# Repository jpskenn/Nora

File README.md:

# Nora（ノラ）

Nora（ノラ）は、Choc v1 ロープロファイルスイッチを使用する、狭ピッチの一体型キーボードです。  
姉妹機[Jones（ジョーンズ）](https://github.com/jpskenn/Jones)と同様の、2行目と3行目にずれのない左右対称の配列が特徴です。  
専用のボトムプレートや、GH60型，Poker型のロープロファイルケースと組み合わせて使用できます。

名前の由来は、”狭ピッチのJonesキーボード”からの連想で…

``` text
狭ピッチのJones → ナロー・ジョーンズ → ノラ・ジョーンズ → ノラ

Narrow Jones --> Norah Jones --> Norah --> Nora
```

という具合の言葉遊びで、Nora（ノラ）に決まりました。

Nora is a narrow pitch keyboard with Choc v1 low profile switches.  
It has symmetrical gapless R2-R3 row, like [Jones](https://github.com/jpskenn/Jones).  
Original bottom plate and GH60/Poker compatible low profile cases are supported.

---

<!-- @import "[TOC]" {cmd="toc" depthFrom=2 depthTo=2 orderedList=false} -->

<!-- code_chunk_output -->

- [対象とするユーザー](#対象とするユーザー)
- [コンセプト](#コンセプト)
- [特徴](#特徴)
- [機能](#機能)
- [ビルドガイド](#ビルドガイド)
- [ビルド例](#ビルド例)
- [製作歴](#製作歴)

<!-- /code_chunk_output -->

---

## 対象とするユーザー

このNoraキーボードは、  
*”一般的なキーボードのキー配列に不満があり、より良いタイピングポジションを求めている方”*  
を対象に作られています。

特に、  
*”一般的なキーボードと違いすぎないキーボードを求めている方”*  
におすすめします。

## コンセプト

- 「Chocスイッチの狭ピッチを60%ケースに入れたら、1列増えて65%キーボードができちゃうのでは？」という思いつき。
- 一般的なキーピッチの19.05mmで打鍵がつらいのを、狭ピッチで楽にしたい。
- 「狭ピッチは浅いストロークの方が打鍵しやすい」という経験から、Chocスイッチを採用。
- MBKキーキャップって格好良いじゃんか。
- Jonesの横方向（行方向）のずれかたや、左右対称のアルファ部に満足している。
- 一般的なキーボードのレイアウトから大きく変えずに、打鍵しやすくする。
- キー数は60%くらいで、数字行がついているものが使いたい。
- GH60型のケースに対応させ、ケース設計をメイン作業に含めない。
- これくらいの狭ピッチなら、通常のキーボードと何ら変わらず打鍵できることを伝えたい。

## 特徴

### 狭ピッチ

Kailh Chocスイッチとそれに対応するキーキャップを使用することで、一般的なキーボードよりもキーピッチが狭くなっています。

60%キーボードのサイズに16列を配置するため、Choc用キーキャップのキーピッチ（たて17mm×よこ18mm）よりも横方向を少し狭く（たて17mm×よこ約17.86mm）しています。  
横方向のキーピッチは、MBKまたはそれ以下のサイズのChoc用キーキャップの使用を前提とした設計です。

キーピッチの比較  
上：一般的なキーピッチの60%キーボード、HHKB Professional。5行15列。  
下：狭ピッチ設計のNora。5行**16列**（1列多い）。

### 左右対称のキーレイアウト

キーレイアウトは[Jones](https://github.com/jpskenn/Jones)のレイアウトを元に設計しており、2行目と3行目にずれのない左右対称のキーレイアウトです。  

Jones（上）とNora（下）。  
どちらも2行目と3行目にずれがなく、左右対称。

詳しくは次の項目を参照してください。

- [Jones#独自のずれ幅をもつ左右対象のアルファ部](https://github.com/jpskenn/Jones#独自のずれ幅をもつ左右対象のアルファ部)

### レイアウトのスタイル、バリエーション

狭ピッチの一体型キーボードというコンセプトを元に、ふたつのレイアウトスタイルを作成しました。

- Nora, Fearless Wings
- Nora, 1.8k

各スタイルの特徴は以下の通りです。

#### Nora, Fearless Wings

左右に大きく離れたアルファ部が特徴のレイアウトスタイルです。  
[Keyboard Layout Editor: Nora, Fearless Wings family](http://www.keyboard-layout-editor.com/#/gists/568990362f215776aa93e3b90064f241)

アルファ部を左右へ大きく離すことで打鍵時の肘・腕・手首・指先の位置を最適化し、快適な運指と、肩や腕への負担軽減を目指しています。  
手首をあまり持ち上げないスタイルでも快適に打鍵できるように、最下行の左右の端にはキーを配置せず、手のひらにキーが当たる不快感を無くしています。  
`Z`キーを外側へずらして、[SemiErgo](https://github.com/mtei/SemiErgo_Layout)のような完全に左右対称のレイアウトも構成できます。

キー配置とロータリーエンコーダの有無により、3つのバリエーションがあります。

- Fullレイアウト

    左右に離れたアルファ部の間を、すべて埋めたレイアウトです。  
    65〜70%キーボードに相当する71個のキーは、多くのキーを必要とする方に適しています。  
    中央部に記号キーやカーソルを配置したり、テンキーやマクロキーを配置したりできます。

- FWレイアウト

    Fullレイアウトから中央部の7キーを取り除き、真ん中に隙間のあるレイアウトです。  
    60%キーボードに相当する64キーをもち、必要十分なキー数を確保しています。  
    ホームポジションから手を移動させず、レイヤー内のキーを打鍵するのが快適な方に適しています。  

- REレイアウト

    FWレイアウトの中央にロータリーエンコーダを配置したレイアウトです。  
    4行目の中央をFWレイアウトから2キー減らし、直径35ｍｍまでのノブに対応しています。

#### Nora, 1.8k

アルファ部の右側にテンキーを配置し、少し下へ飛びだしたカーソルキーが特徴のレイアウトスタイルです。  
[Keyboard Layout Editor: Nora](http://www.keyboard-layout-editor.com/#/gists/f8d08df6aa77dcdd6d3cb7350a545df7)

一般的なキーボードをコンパクトにまとめたようなキー配置になっています。  
キー数が多く、記号やカーソルなどを物理的に配置することができます。

試作版でロードテストをおこなった結果、狭ピッチで左右の手が中央へ近づいて肩や腕、親指まわりが窮屈になり、長時間の使用には向かないことがわかりました。  
日常的に使用する上での快適さを満たせないため、1.8kは開発を停止しています。

## 機能

### QMKファームウェアによる動作

MCUにATmega32u4を採用し、[QMKファームウェア](https://github.com/qmk/qmk_firmware)によって動作します。

### RemapやVIAなどのキーマップ書き換えツールに対応

[Remap](https://remap-keys.app)や[VIA](https://caniusevia.com)などのキーマップ書き換えツールに対応しており、ファームウェアを書き換えることなく、キーの割り当てを変更することができます。  

### EEPROM搭載により、多くのレイヤーを使用可能

外部EEPROMを搭載したことで、RemapやVIA使用時にも多くのレイヤーを使用することができます。  
出荷時に書き込まれている初期ファームウェアでは、10個のレイヤーを使用可能です。  

### ケース

キット同梱のボトムプレートと組み合わせれば、ケースレスで使用できます。  
ケースを使用する場合に比べてキーボードの高さを低く抑えることができ、手首の負担軽減などに有効です。

また、GH60型やPoker型に互換性のある、ロープロファイルケースと組み合わせて使用することもできます。  
→[ビルド例](#ビルド例)  

### フルキーバックライトLED

レイヤーの状態を表示するインジケータや、イルミネーションとして使用できるキーバックライトLEDを、すべてのキーへ取り付けできます。

### Raspberry Pi PICOによる動作（実験的機能）

実験的機能として、Raspberry Pi PICOで動作させることができます。  
キーマトリクス、LED、I2Cに配線をつないであるので、DIYで楽しんでください。

[PRK Firmware](https://github.com/picoruby/prk_firmware)を使用して、キー入力とLEDの点灯を確認済みです。

## ビルドガイド

- 最新版
  - [Nora, Fearless Wings v.1(DN0032) ビルドガイド](./docs/BuildGuide_DN0032_JA.md)

- 過去版
  - [Nora, Fearless Wings DN0031 ビルドガイド](./docs/BuildGuide_DN0031_JA.md)
  - [Nora, Fearless Wings DN0030 ビルドガイド](./docs/BuildGuide_DN0030_JA.md)
  - [Nora, 1.8k v.0.1 ビルドガイド](./docs/BuildGuide_v.0.1_JA.md)

</details>

## ビルド例

| ビルド例 | 詳細 |
| --- | :-- |
|  | v.1(DN0032)<br>layout: Full<br>keycaps: MBK Legend‡ Glow<br>case: Bottom plate |
|  | DN0031<br>layout: FW<br>keycaps: Kailh low profile + MBK<br>case: Bottom plate |
|  | DN0031<br>layout: RE<br>keycaps: Gravity Keycaps + MBK<br>case: KBDfans 60% Aluminum Low Profile, Gray |
|  | DN0020<br>layout: 1.8k<br>keycaps: MBK Colors & Self Dye<br>case: KBDfans 60% Aluminum Low Profile, Gray |
|  | DN0010<br>layout: 1.8k<br>keycaps: Kailh low profile<br>case: Bottom plate |

## 製作歴

- Fearless Wings v.1(DN0032), 2022年3月中旬

    組み立てやすさを向上。  
    ロータリーエンコーダのノブサイズ拡大のため、REレイアウトの最下行中央のキーを削除。  
    細部を調整。  
    DN0031組み立てアンケートの内容を反映。

- Fearless Wings DN0031, 2022年1月下旬

    スペースキーより内側のキーに親指が届きやすいように、最下行を外側へ0.25u移動。  
    ロータリーエンコーダ付きのレイアウトを追加。  
    組み立てやすさを向上。
    少数頒布。

- Fearless Wings DN0030, 2022年1月上旬

    DN0020を元にレイアウトを変更。  
    全キーへLEDを配置。  
    Jonesとの共用ボトムプレートを、PICOの取り付けに対応する切り欠きをつけて更新。

- 1.8k DN0020, 2021年12月中旬

    1.8k v.0.1の試作結果を反映。  
    全キーをKailhソケットに変更。  
    現在のところ基板設計のみ。未製造。

- 1.8k v.0.1, 2021年12月上旬

    試作1号機、完成。

- 1.8k v.0, 2021年11月上旬

    60%ケースにChocスイッチを配置して、65%キーボードにするアイデアを思いつく。

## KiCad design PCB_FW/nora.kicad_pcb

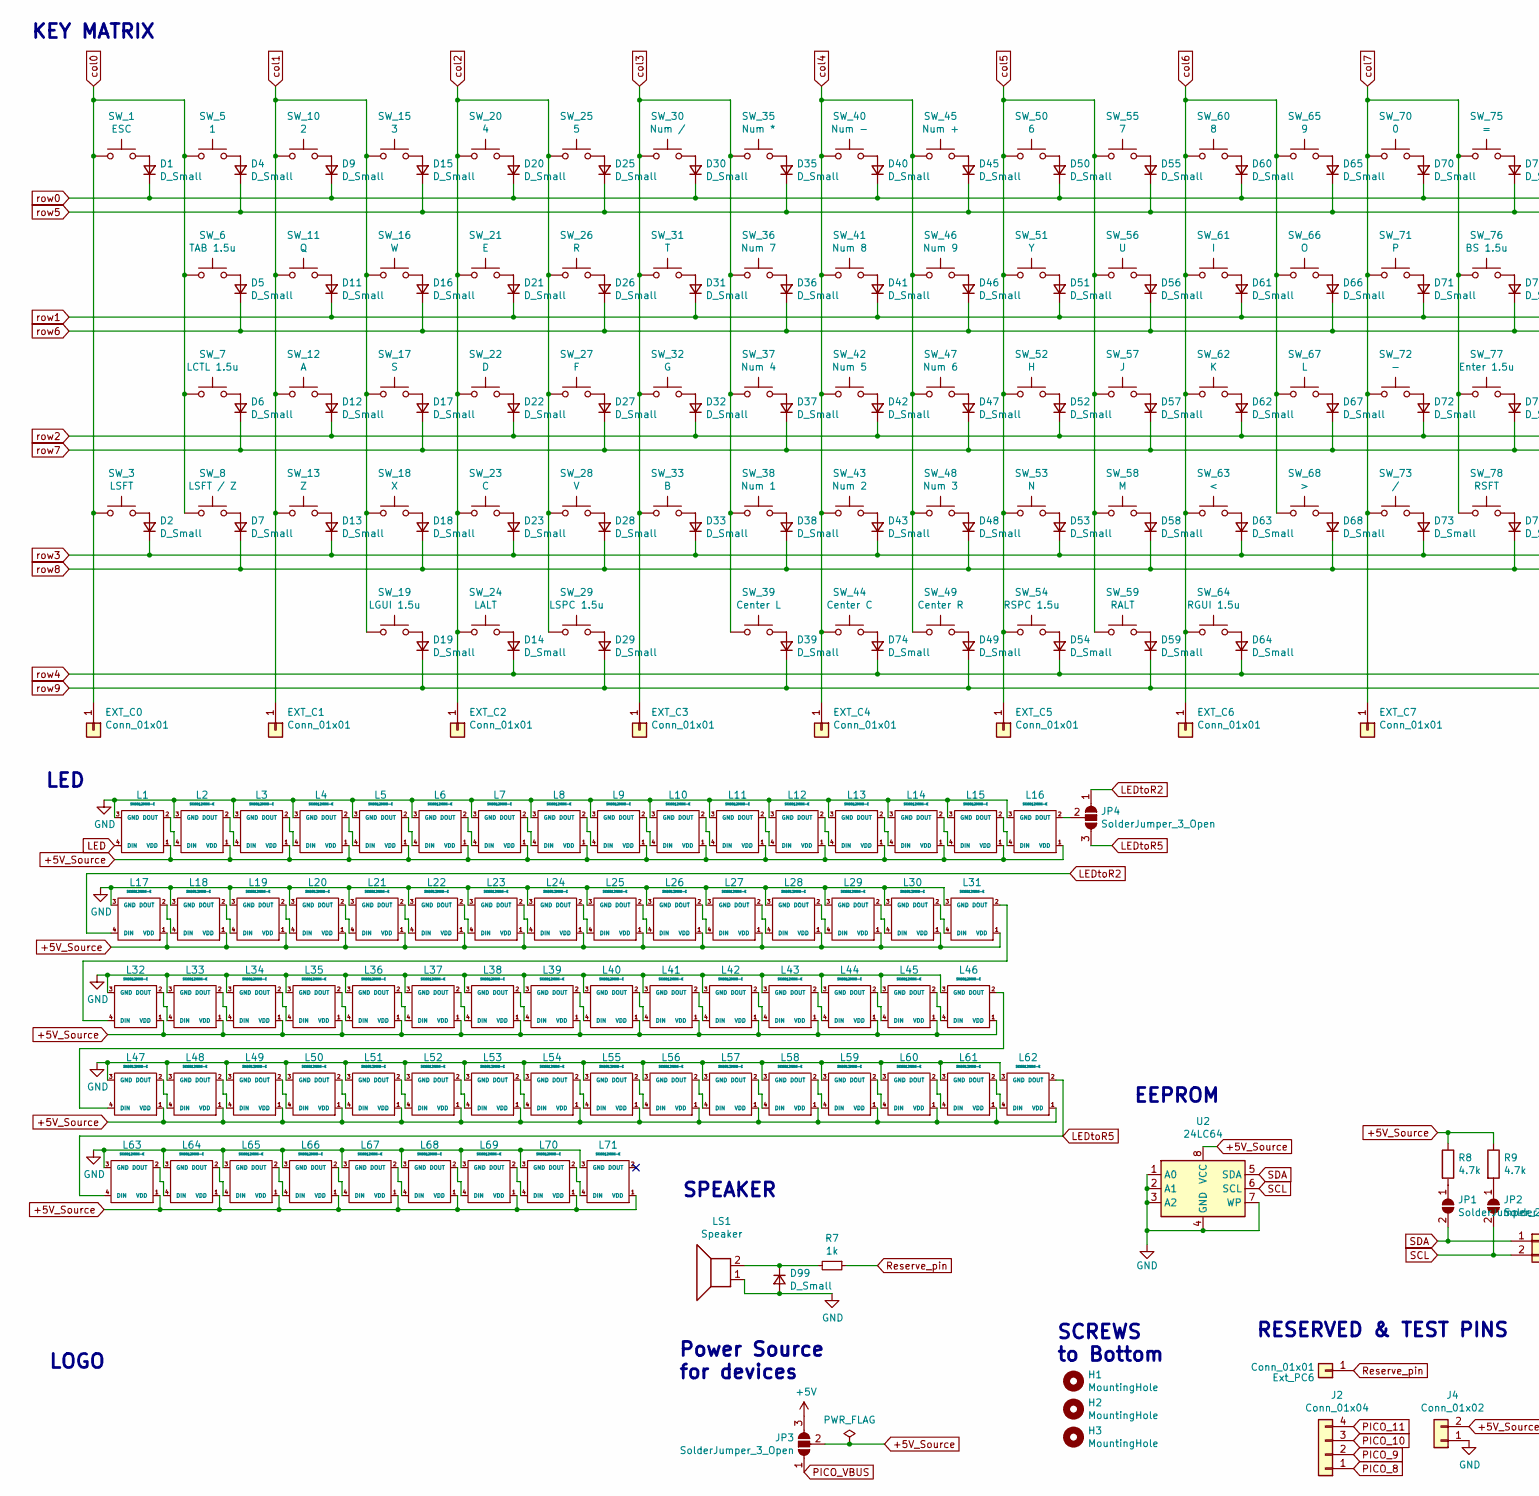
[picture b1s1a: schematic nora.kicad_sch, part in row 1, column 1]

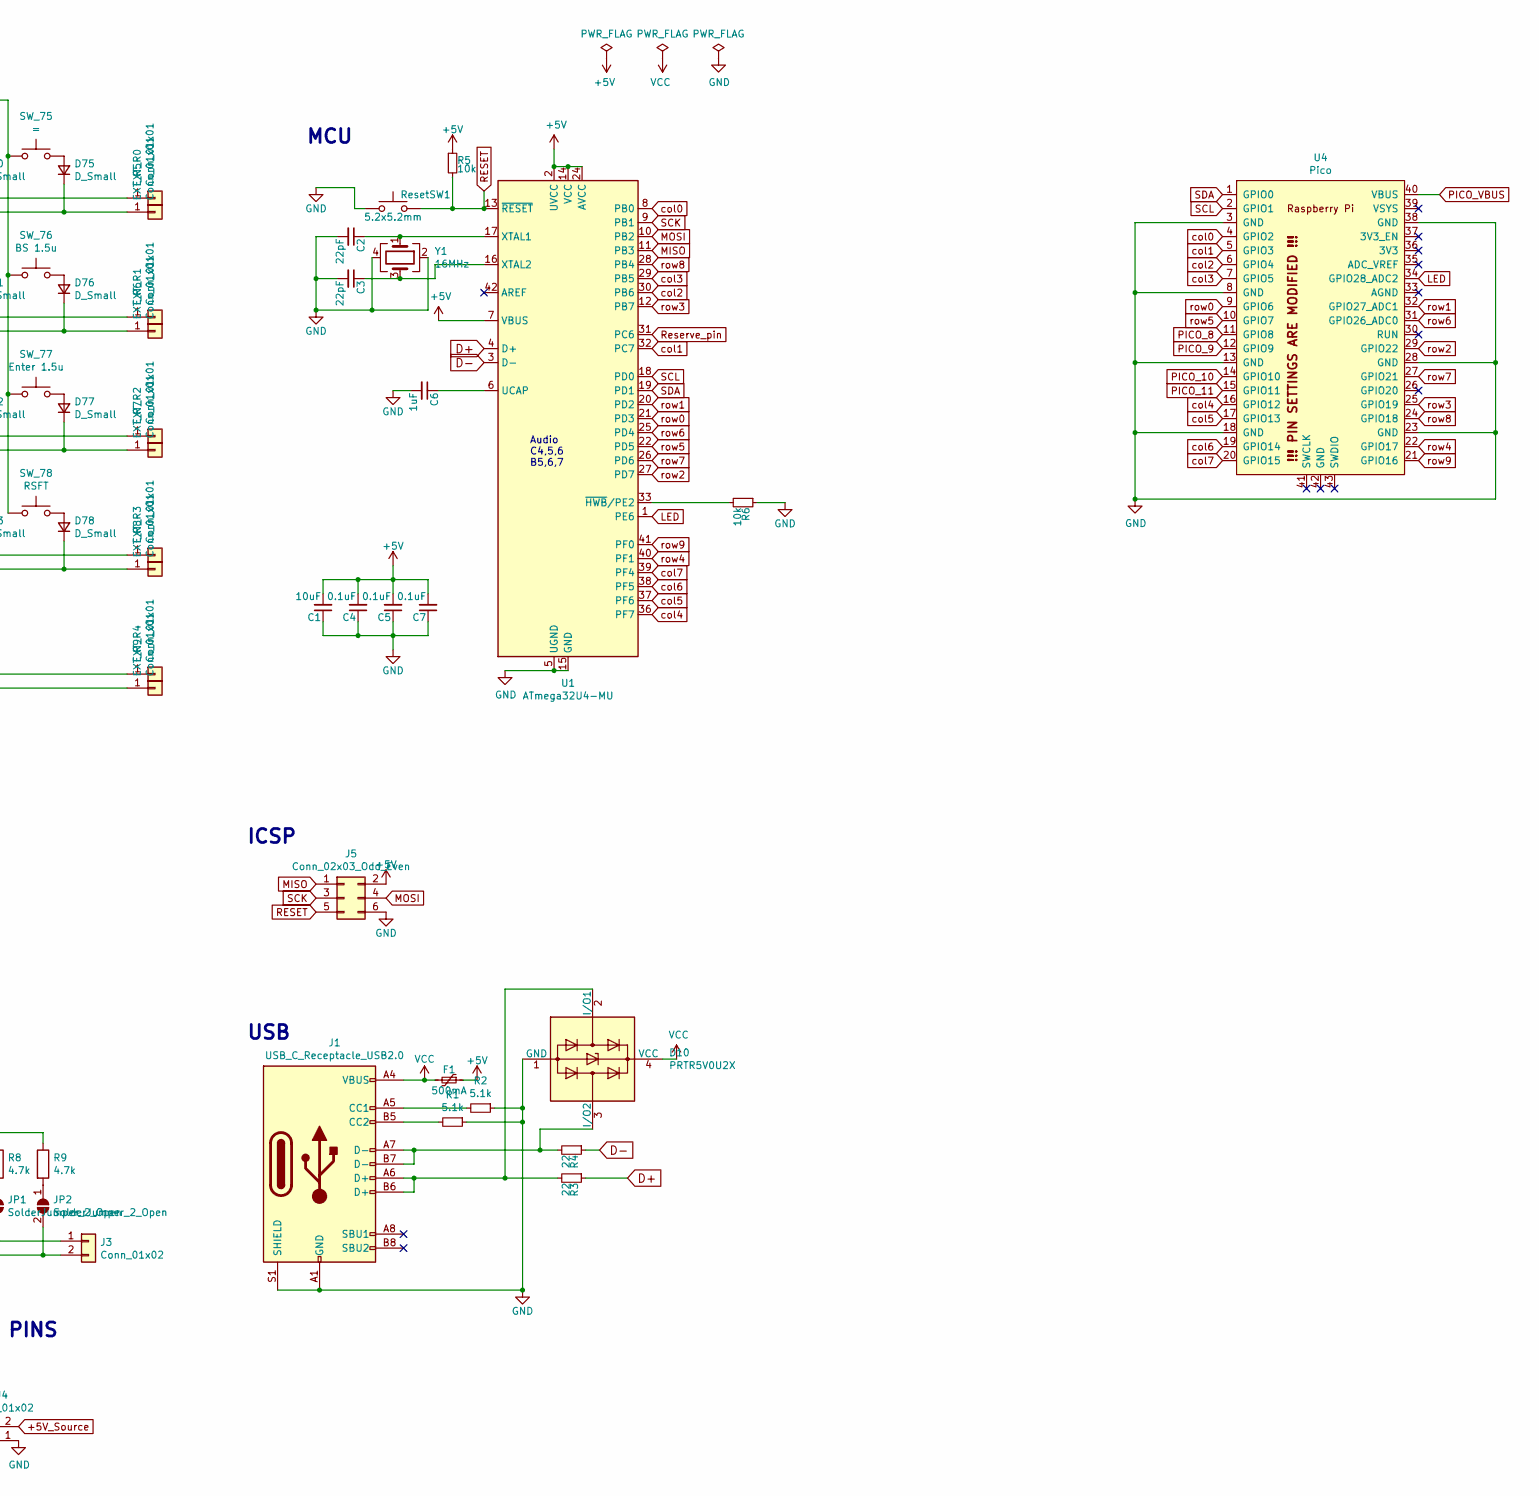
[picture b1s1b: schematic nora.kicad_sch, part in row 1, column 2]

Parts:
C1: 10uF; C_0805_2012Metric_Pad1.18x1.45mm_HandSolder; LCSC C15850
C2, C3: 22pF; C_0805_2012Metric_Pad1.18x1.45mm_HandSolder; LCSC C1804
C4, C5, C7: 0.1uF; C_0805_2012Metric_Pad1.18x1.45mm_HandSolder; LCSC C49678
C6: 1uF; C_0805_2012Metric_Pad1.18x1.45mm_HandSolder; LCSC C28323
D1, D2, D4, D5, D6, D7, D9, D11, D12, D13, D14, D15, D16, D17, D18, D19, D20, D21, D22, D23, D25, D26, D27, D28, D29, D30, D31, D32, D33, D35, D36, D37, D38, D39, D40, D41, D42, D43, D45, D46, D47, D48, D49, D50, D51, D52, D53, D54, D55, D56, D57, D58, D59, D60, D61, D62, D63, D64, D65, D66, D67, D68, D70, D71, D72, D73, D74, D75, D76, D77, D78: D_Small; D_SOD-123-Pretty_No_Reference; LCSC C81598
D10: PRTR5V0U2X; SOT-143; LCSC C78442
D99: D_Small; D_SOD-123-Pretty_No_Reference
EXT_C0, EXT_C1, EXT_C2, EXT_C3, EXT_C4, EXT_C5, EXT_C6, EXT_C7: Conn_01x01; TestPoint_THTPad_D1.5mm_Drill0.7mm
EXT_R0, EXT_R1, EXT_R2, EXT_R3, EXT_R4, EXT_R5, EXT_R6, EXT_R7, EXT_R8, EXT_R9: Conn_01x01; TestPoint_THTPad_D1.5mm_Drill0.7mm
Ext_PC6: Conn_01x01; TestPoint_THTPad_D1.0mm_Drill0.5mm
F1: 500mA; Fuse_1206_3216Metric_Pad1.42x1.75mm_HandSolder; LCSC C70076
H1, H2, H3: MountingHole; MountingHole_2.2mm_M2
J1: USB_C_Receptacle_USB2.0; USB_C_Receptacle_GCT_USB4085
J2: Conn_01x04; PinHeader_1x04_P2.54mm_Vertical
J3, J4: Conn_01x02; PinHeader_1x02_P2.54mm_Vertical
J5: Conn_02x03_Odd_Even; PinHeader_2x03_P2.54mm_Vertical
JP1, JP2: SolderJumper_2_Open; SolderJumper-2_P1.3mm_Open_RoundedPad1.0x1.5mm
JP3, JP4: SolderJumper_3_Open; SolderJumper-3_P1.3mm_Open_RoundedPad1.0x1.5mm
L1, L2, L3, L4, L5, L6, L7, L8, L9, L10, L11, L12, L13, L14, L15, L16, L17, L18, L19, L20, L21, L22, L23, L24, L25, L26, L27, L28, L29, L30, L31, L32, L33, L34, L35, L36, L37, L38, L39, L40, L41, L42, L43, L44, L45, L46, L47, L48, L49, L50, L51, L52, L53, L54, L55, L56, L57, L58, L59, L60, L61, L62, L63, L64, L65, L66, L67, L68, L69, L70, L71: SK6812MINI-E; YS-SK6812MINI-E_with_reflection_paint
LS1: Speaker; Buzzer_Murata_PKMCS0909E4000-R1
R1, R2: 5.1k; R_0805_2012Metric_Pad1.20x1.40mm_HandSolder; LCSC C27834
R3, R4: 22; R_0805_2012Metric_Pad1.20x1.40mm_HandSolder; LCSC C17561
R5, R6: 10k; R_0805_2012Metric_Pad1.20x1.40mm_HandSolder; LCSC C17414
R7: 1k; R_0805_2012Metric_Pad1.20x1.40mm_HandSolder
R8, R9: 4.7k; R_0805_2012Metric_Pad1.20x1.40mm_HandSolder; LCSC C17673
ResetSW1: 5.2x5.2mm; SW_SPST_TL3342
SW_1: ESC; Kailh-PG1350-1u-MBK-WithKeyName-Socket-ForLeftEdge2
SW_3: LSFT; Kailh-PG1350-1u-MBK-WithKeyName-Socket-ForLeftEdge2
SW_5: 1; Kailh-PG1350-1u-MBK-WithKeyName-Socket
SW_6: TAB 1.5u; Kailh-PG1350-1.5u-MBK-WithKeyName-Socket
SW_7: LCTL 1.5u; Kailh-PG1350-1.5u-MBK-WithKeyName-Socket
SW_8: LSFT / Z; Kailh-PG1350-1u-MBK-WithKeyName-Socket
SW_10: 2; Kailh-PG1350-1u-MBK-WithKeyName-Socket
SW_11: Q; Kailh-PG1350-1u-MBK-WithKeyName-Socket
SW_12: A; Kailh-PG1350-1u-MBK-WithKeyName-Socket
SW_13: Z; Kailh-PG1350-1u-MBK-WithKeyName-Socket
SW_15: 3; Kailh-PG1350-1u-MBK-WithKeyName-Socket
SW_16: W; Kailh-PG1350-1u-MBK-WithKeyName-Socket
SW_17: S; Kailh-PG1350-1u-MBK-WithKeyName-Socket
SW_18: X; Kailh-PG1350-1u-MBK-WithKeyName-Socket
SW_19: LGUI 1.5u; Kailh-PG1350-1.5u-MBK-WithKeyName-Socket
SW_20: 4; Kailh-PG1350-1u-MBK-WithKeyName-Socket
SW_21: E; Kailh-PG1350-1u-MBK-WithKeyName-Socket
SW_22: D; Kailh-PG1350-1u-MBK-WithKeyName-Socket
SW_23: C; Kailh-PG1350-1u-MBK-WithKeyName-Socket
SW_24: LALT; Kailh-PG1350-1u-MBK-WithKeyName-Socket
SW_25: 5; Kailh-PG1350-1u-MBK-WithKeyName-Socket
SW_26: R; Kailh-PG1350-1u-MBK-WithKeyName-Socket
SW_27: F; Kailh-PG1350-1u-MBK-WithKeyName-Socket
SW_28: V; Kailh-PG1350-1u-MBK-WithKeyName-Socket
SW_29: LSPC 1.5u; Kailh-PG1350-1.5u-MBK-WithKeyName-Socket
SW_30: Num /; Kailh-PG1350-1u-MBK-WithKeyName-Socket
SW_31: T; Kailh-PG1350-1u-MBK-WithKeyName-Socket
SW_32: G; Kailh-PG1350-1u-MBK-WithKeyName-Socket
SW_33: B; Kailh-PG1350-1u-MBK-WithKeyName-Socket
SW_35: Num *; Kailh-PG1350-1u-MBK-WithKeyName-Socket
SW_36: Num 7; Kailh-PG1350-1u-MBK-WithKeyName-Socket
SW_37: Num 4; Kailh-PG1350-1u-MBK-WithKeyName-Socket
SW_38: Num 1; Kailh-PG1350-1u-MBK-WithKeyName-Socket
SW_39: Center L; Kailh-PG1350-1u-MBK-WithKeyName-Socket
SW_40: Num -; Kailh-PG1350-1u-MBK-WithKeyName-Socket
SW_41: Num 8; Kailh-PG1350-1u-MBK-WithKeyName-Socket
SW_42: Num 5; Kailh-PG1350-1u-MBK-WithKeyName-Socket
SW_43: Num 2; Kailh-PG1350-1u-MBK-WithKeyName-Socket
SW_44: Center C; Kailh-PG1350-1u-MBK-WithKeyName-Socket
SW_45: Num +; Kailh-PG1350-1u-MBK-WithKeyName-Socket
SW_46: Num 9; Kailh-PG1350-1u-MBK-WithKeyName-Socket
SW_47: Num 6; Kailh-PG1350-1u-MBK-WithKeyName-Socket
SW_48: Num 3; Kailh-PG1350-1u-MBK-WithKeyName-Socket
SW_49: Center R; Kailh-PG1350-1u-MBK-WithKeyName-Socket
SW_50: 6; Kailh-PG1350-1u-MBK-WithKeyName-Socket
SW_51: Y; Kailh-PG1350-1u-MBK-WithKeyName-Socket
SW_52: H; Kailh-PG1350-1u-MBK-WithKeyName-Socket
SW_53: N; Kailh-PG1350-1u-MBK-WithKeyName-Socket
SW_54: RSPC 1.5u; Kailh-PG1350-1.5u-MBK-WithKeyName-Socket
SW_55: 7; Kailh-PG1350-1u-MBK-WithKeyName-Socket
SW_56: U; Kailh-PG1350-1u-MBK-WithKeyName-Socket
SW_57: J; Kailh-PG1350-1u-MBK-WithKeyName-Socket
SW_58: M; Kailh-PG1350-1u-MBK-WithKeyName-Socket
SW_59: RALT; Kailh-PG1350-1u-MBK-WithKeyName-Socket
SW_60: 8; Kailh-PG1350-1u-MBK-WithKeyName-Socket
SW_61: I; Kailh-PG1350-1u-MBK-WithKeyName-Socket
SW_62: K; Kailh-PG1350-1u-MBK-WithKeyName-Socket
SW_63: <; Kailh-PG1350-1u-MBK-WithKeyName-Socket
SW_64: RGUI 1.5u; Kailh-PG1350-1.5u-MBK-WithKeyName-Socket
SW_65: 9; Kailh-PG1350-1u-MBK-WithKeyName-Socket
SW_66: O; Kailh-PG1350-1u-MBK-WithKeyName-Socket
SW_67: L; Kailh-PG1350-1u-MBK-WithKeyName-Socket
SW_68: >; Kailh-PG1350-1u-MBK-WithKeyName-Socket
SW_70: 0; Kailh-PG1350-1u-MBK-WithKeyName-Socket
SW_71: P; Kailh-PG1350-1u-MBK-WithKeyName-Socket
SW_72: -; Kailh-PG1350-1u-MBK-WithKeyName-Socket
SW_73: /; Kailh-PG1350-1u-MBK-WithKeyName-Socket
SW_75: =; Kailh-PG1350-1u-MBK-WithKeyName-Socket
SW_76: BS 1.5u; Kailh-PG1350-1.5u-MBK-WithKeyName-Socket
SW_77: Enter 1.5u; Kailh-PG1350-1.5u-MBK-WithKeyName-Socket
SW_78: RSFT; Kailh-PG1350-1u-MBK-WithKeyName-Socket
U1: ATmega32U4-MU; QFN-44-1EP_7x7mm_P0.5mm_EP5.2x5.2mm; LCSC C45874
U2: 24LC64; SO-8_3.9x4.9mm_P1.27mm; LCSC C79988
U4: Pico; RPi_Pico_TH_no_NPTH_SWD_less_Silk_NoCrtYd
Y1: 16MHz; Crystal_SMD_3225-4Pin_3.2x2.5mm_HandSoldering; LCSC C13738

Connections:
+5V: C1.2, C4.2, C5.2, C7.2, F1.1, J5.2, JP3.3 (B), R5.1, U1.2 (UVCC), U1.7 (VBUS), U1.14 (VCC), U1.24 (AVCC), U1.34 (VCC), U1.44 (AVCC)
+5V_Source: J4.2, JP3.2 (C), L1.1 (VDD), L2.1 (VDD), L3.1 (VDD), L4.1 (VDD), L5.1 (VDD), L6.1 (VDD), L7.1 (VDD), L8.1 (VDD), L9.1 (VDD), L10.1 (VDD), L11.1 (VDD), L12.1 (VDD), L13.1 (VDD), L14.1 (VDD), L15.1 (VDD), L16.1 (VDD), L17.1 (VDD), L18.1 (VDD), L19.1 (VDD), L20.1 (VDD), L21.1 (VDD), L22.1 (VDD), L23.1 (VDD), L24.1 (VDD), L25.1 (VDD), L26.1 (VDD), L27.1 (VDD), L28.1 (VDD), L29.1 (VDD), L30.1 (VDD), L31.1 (VDD), L32.1 (VDD), L33.1 (VDD), L34.1 (VDD), L35.1 (VDD), L36.1 (VDD), L37.1 (VDD), L38.1 (VDD), L39.1 (VDD), L40.1 (VDD), L41.1 (VDD), L42.1 (VDD), L43.1 (VDD), L44.1 (VDD), L45.1 (VDD), L46.1 (VDD), L47.1 (VDD), L48.1 (VDD), L49.1 (VDD), L50.1 (VDD), L51.1 (VDD), L52.1 (VDD), L53.1 (VDD), L54.1 (VDD), L55.1 (VDD), L56.1 (VDD), L57.1 (VDD), L58.1 (VDD), L59.1 (VDD), L60.1 (VDD), L61.1 (VDD), L62.1 (VDD), L63.1 (VDD), L64.1 (VDD), L65.1 (VDD), L66.1 (VDD), L67.1 (VDD), L68.1 (VDD), L69.1 (VDD), L70.1 (VDD), L71.1 (VDD), R8.1, R9.1, U2.8 (VCC)
D+: R3.1, U1.4 (D+)
D-: R4.1, U1.3 (D-)
GND: C1.1, C2.2, C3.2, C4.1, C5.1, C6.2, C7.1, D10.1 (GND), D99.2 (A), J1.A1 (GND), J1.A12 (GND), J1.B1 (GND), J1.B12 (GND), J1.S1 (SHIELD), J4.1, J5.6, L1.3 (GND), L2.3 (GND), L3.3 (GND), L4.3 (GND), L5.3 (GND), L6.3 (GND), L7.3 (GND), L8.3 (GND), L9.3 (GND), L10.3 (GND), L11.3 (GND), L12.3 (GND), L13.3 (GND), L14.3 (GND), L15.3 (GND), L16.3 (GND), L17.3 (GND), L18.3 (GND), L19.3 (GND), L20.3 (GND), L21.3 (GND), L22.3 (GND), L23.3 (GND), L24.3 (GND), L25.3 (GND), L26.3 (GND), L27.3 (GND), L28.3 (GND), L29.3 (GND), L30.3 (GND), L31.3 (GND), L32.3 (GND), L33.3 (GND), L34.3 (GND), L35.3 (GND), L36.3 (GND), L37.3 (GND), L38.3 (GND), L39.3 (GND), L40.3 (GND), L41.3 (GND), L42.3 (GND), L43.3 (GND), L44.3 (GND), L45.3 (GND), L46.3 (GND), L47.3 (GND), L48.3 (GND), L49.3 (GND), L50.3 (GND), L51.3 (GND), L52.3 (GND), L53.3 (GND), L54.3 (GND), L55.3 (GND), L56.3 (GND), L57.3 (GND), L58.3 (GND), L59.3 (GND), L60.3 (GND), L61.3 (GND), L62.3 (GND), L63.3 (GND), L64.3 (GND)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
LED: L1.4 (DIN), U1.1 (PE6), U4.34 (GPIO28_ADC2)
LEDtoR2: JP4.1 (A), L17.4 (DIN)
LEDtoR5: JP4.3 (B), L62.2 (DOUT), L63.4 (DIN)
MISO: J5.1, U1.11 (PB3)
MOSI: J5.4, U1.10 (PB2)
unnamed: C2.1, U1.17 (XTAL1), Y1.1
unnamed: C3.1, U1.16 (XTAL2), Y1.3
unnamed: C6.1, U1.6 (UCAP)
unnamed: D1.2 (A), SW_1.2
unnamed: D2.2 (A), SW_3.2
unnamed: D4.2 (A), SW_5.2
unnamed: D5.2 (A), SW_6.2
unnamed: D6.2 (A), SW_7.2
unnamed: D7.2 (A), SW_8.2
unnamed: D9.2 (A), SW_10.2
unnamed: D10.2 (I/O1), J1.A6 (D+), J1.B6 (D+), R3.2
unnamed: D10.3 (I/O2), J1.A7 (D-), J1.B7 (D-), R4.2
unnamed: D11.2 (A), SW_11.2
unnamed: D12.2 (A), SW_12.2
unnamed: D13.2 (A), SW_13.2
unnamed: D14.2 (A), SW_24.2
unnamed: D15.2 (A), SW_15.2
unnamed: D16.2 (A), SW_16.2
unnamed: D17.2 (A), SW_17.2
unnamed: D18.2 (A), SW_18.2
unnamed: D19.2 (A), SW_19.2
unnamed: D20.2 (A), SW_20.2
unnamed: D21.2 (A), SW_21.2
unnamed: D22.2 (A), SW_22.2
unnamed: D23.2 (A), SW_23.2
unnamed: D25.2 (A), SW_25.2
unnamed: D26.2 (A), SW_26.2
unnamed: D27.2 (A), SW_27.2
unnamed: D28.2 (A), SW_28.2
unnamed: D29.2 (A), SW_29.2
unnamed: D30.2 (A), SW_30.2
unnamed: D31.2 (A), SW_31.2
unnamed: D32.2 (A), SW_32.2
unnamed: D33.2 (A), SW_33.2
unnamed: D35.2 (A), SW_35.2
unnamed: D36.2 (A), SW_36.2
unnamed: D37.2 (A), SW_37.2
unnamed: D38.2 (A), SW_38.2
unnamed: D39.2 (A), SW_39.2
unnamed: D40.2 (A), SW_40.2
unnamed: D41.2 (A), SW_41.2
unnamed: D42.2 (A), SW_42.2
unnamed: D43.2 (A), SW_43.2
unnamed: D45.2 (A), SW_45.2
unnamed: D46.2 (A), SW_46.2
unnamed: D47.2 (A), SW_47.2
unnamed: D48.2 (A), SW_48.2
unnamed: D49.2 (A), SW_49.2
unnamed: D50.2 (A), SW_50.2
unnamed: D51.2 (A), SW_51.2
unnamed: D52.2 (A), SW_52.2
unnamed: D53.2 (A), SW_53.2
unnamed: D54.2 (A), SW_54.2
unnamed: D55.2 (A), SW_55.2
unnamed: D56.2 (A), SW_56.2
unnamed: D57.2 (A), SW_57.2
unnamed: D58.2 (A), SW_58.2
unnamed: D59.2 (A), SW_59.2
unnamed: D60.2 (A), SW_60.2
unnamed: D61.2 (A), SW_61.2
unnamed: D62.2 (A), SW_62.2
unnamed: D63.2 (A), SW_63.2
unnamed: D64.2 (A), SW_64.2
unnamed: D65.2 (A), SW_65.2
unnamed: D66.2 (A), SW_66.2
unnamed: D67.2 (A), SW_67.2
unnamed: D68.2 (A), SW_68.2
unnamed: D70.2 (A), SW_70.2
unnamed: D71.2 (A), SW_71.2
unnamed: D72.2 (A), SW_72.2
unnamed: D73.2 (A), SW_73.2
unnamed: D74.2 (A), SW_44.2
unnamed: D75.2 (A), SW_75.2
unnamed: D76.2 (A), SW_76.2
unnamed: D77.2 (A), SW_77.2
unnamed: D78.2 (A), SW_78.2
unnamed: D99.1 (K), LS1.2, R7.2
unnamed: J1.A5 (CC1), R2.2
unnamed: J1.B5 (CC2), R1.2
unnamed: JP1.1 (A), R8.2
unnamed: JP2.1 (A), R9.2
unnamed: JP4.2 (C), L16.2 (DOUT)
unnamed: L1.2 (DOUT), L2.4 (DIN)
unnamed: L2.2 (DOUT), L3.4 (DIN)
unnamed: L3.2 (DOUT), L4.4 (DIN)
unnamed: L4.2 (DOUT), L5.4 (DIN)
unnamed: L5.2 (DOUT), L6.4 (DIN)
unnamed: L6.2 (DOUT), L7.4 (DIN)
unnamed: L7.2 (DOUT), L8.4 (DIN)
unnamed: L8.2 (DOUT), L9.4 (DIN)
unnamed: L10.2 (DOUT), L11.4 (DIN)
unnamed: L9.2 (DOUT), L10.4 (DIN)
unnamed: L11.2 (DOUT), L12.4 (DIN)
unnamed: L12.2 (DOUT), L13.4 (DIN)
unnamed: L13.2 (DOUT), L14.4 (DIN)
unnamed: L14.2 (DOUT), L15.4 (DIN)
unnamed: L15.2 (DOUT), L16.4 (DIN)
unnamed: L17.2 (DOUT), L18.4 (DIN)
unnamed: L18.2 (DOUT), L19.4 (DIN)
unnamed: L19.2 (DOUT), L20.4 (DIN)
unnamed: L20.2 (DOUT), L21.4 (DIN)
unnamed: L21.2 (DOUT), L22.4 (DIN)
unnamed: L22.2 (DOUT), L23.4 (DIN)
unnamed: L23.2 (DOUT), L24.4 (DIN)
unnamed: L24.2 (DOUT), L25.4 (DIN)
unnamed: L25.2 (DOUT), L26.4 (DIN)
unnamed: L26.2 (DOUT), L27.4 (DIN)
unnamed: L27.2 (DOUT), L28.4 (DIN)
unnamed: L28.2 (DOUT), L29.4 (DIN)
unnamed: L29.2 (DOUT), L30.4 (DIN)
unnamed: L30.2 (DOUT), L31.4 (DIN)
unnamed: L31.2 (DOUT), L32.4 (DIN)
unnamed: L32.2 (DOUT), L33.4 (DIN)
unnamed: L33.2 (DOUT), L34.4 (DIN)
unnamed: L34.2 (DOUT), L35.4 (DIN)
unnamed: L35.2 (DOUT), L36.4 (DIN)
unnamed: L36.2 (DOUT), L37.4 (DIN)
unnamed: L37.2 (DOUT), L38.4 (DIN)
unnamed: L38.2 (DOUT), L39.4 (DIN)
unnamed: L39.2 (DOUT), L40.4 (DIN)
unnamed: L40.2 (DOUT), L41.4 (DIN)
unnamed: L41.2 (DOUT), L42.4 (DIN)
unnamed: L42.2 (DOUT), L43.4 (DIN)
unnamed: L43.2 (DOUT), L44.4 (DIN)
unnamed: L44.2 (DOUT), L45.4 (DIN)
unnamed: L45.2 (DOUT), L46.4 (DIN)
unnamed: L46.2 (DOUT), L47.4 (DIN)
unnamed: L47.2 (DOUT), L48.4 (DIN)
unnamed: L48.2 (DOUT), L49.4 (DIN)
unnamed: L49.2 (DOUT), L50.4 (DIN)
unnamed: L50.2 (DOUT), L51.4 (DIN)
unnamed: L51.2 (DOUT), L52.4 (DIN)
unnamed: L52.2 (DOUT), L53.4 (DIN)
unnamed: L53.2 (DOUT), L54.4 (DIN)
unnamed: L54.2 (DOUT), L55.4 (DIN)
unnamed: L55.2 (DOUT), L56.4 (DIN)
unnamed: L56.2 (DOUT), L57.4 (DIN)
unnamed: L57.2 (DOUT), L58.4 (DIN)
unnamed: L58.2 (DOUT), L59.4 (DIN)
unnamed: L59.2 (DOUT), L60.4 (DIN)
unnamed: L60.2 (DOUT), L61.4 (DIN)
unnamed: L61.2 (DOUT), L62.4 (DIN)
unnamed: L63.2 (DOUT), L64.4 (DIN)
unnamed: L64.2 (DOUT), L65.4 (DIN)
unnamed: L65.2 (DOUT), L66.4 (DIN)
unnamed: L66.2 (DOUT), L67.4 (DIN)
unnamed: L67.2 (DOUT), L68.4 (DIN)
unnamed: L68.2 (DOUT), L69.4 (DIN)
unnamed: L69.2 (DOUT), L70.4 (DIN)
unnamed: L70.2 (DOUT), L71.4 (DIN)
unnamed: R6.2, U1.33 (~HWB/PE2)
PICO_8: J2.1, U4.11 (GPIO8)
PICO_9: J2.2, U4.12 (GPIO9)
PICO_10: J2.3, U4.14 (GPIO10)
PICO_11: J2.4, U4.15 (GPIO11)
PICO_VBUS: JP3.1 (A), U4.40 (VBUS)
RESET: J5.5, R5.2, ResetSW1.2, U1.13 (~RESET)
Reserve_pin: Ext_PC6.1, R7.1, U1.31 (PC6)
SCK: J5.3, U1.9 (PB1)
SCL: J3.2, JP2.2 (B), U1.18 (PD0), U2.6 (SCL), U4.2 (GPIO1)
SDA: J3.1, JP1.2 (B), U1.19 (PD1), U2.5 (SDA), U4.1 (GPIO0)
VCC: D10.4 (VCC), F1.2, J1.A4 (VBUS), J1.A9 (VBUS), J1.B4 (VBUS), J1.B9 (VBUS)
col0: EXT_C0.1, SW_1.1, SW_3.1, SW_5.1, SW_6.1, SW_7.1, SW_8.1, U1.8 (PB0), U4.4 (GPIO2)
col1: EXT_C1.1, SW_10.1, SW_11.1, SW_12.1, SW_13.1, SW_15.1, SW_16.1, SW_17.1, SW_18.1, SW_19.1, U1.32 (PC7), U4.5 (GPIO3)
col2: EXT_C2.1, SW_20.1, SW_21.1, SW_22.1, SW_23.1, SW_24.1, SW_25.1, SW_26.1, SW_27.1, SW_28.1, SW_29.1, U1.30 (PB6), U4.6 (GPIO4)
col3: EXT_C3.1, SW_30.1, SW_31.1, SW_32.1, SW_33.1, SW_35.1, SW_36.1, SW_37.1, SW_38.1, SW_39.1, U1.29 (PB5), U4.7 (GPIO5)
col4: EXT_C4.1, SW_40.1, SW_41.1, SW_42.1, SW_43.1, SW_44.1, SW_45.1, SW_46.1, SW_47.1, SW_48.1, SW_49.1, U1.36 (PF7), U4.16 (GPIO12)
col5: EXT_C5.1, SW_50.1, SW_51.1, SW_52.1, SW_53.1, SW_54.1, SW_55.1, SW_56.1, SW_57.1, SW_58.1, SW_59.1, U1.37 (PF6), U4.17 (GPIO13)
col6: EXT_C6.1, SW_60.1, SW_61.1, SW_62.1, SW_63.1, SW_64.1, SW_65.1, SW_66.1, SW_67.1, SW_68.1, U1.38 (PF5), U4.19 (GPIO14)
col7: EXT_C7.1, SW_70.1, SW_71.1, SW_72.1, SW_73.1, SW_75.1, SW_76.1, SW_77.1, SW_78.1, U1.39 (PF4), U4.20 (GPIO15)
row0: D1.1 (K), D9.1 (K), D20.1 (K), D30.1 (K), D40.1 (K), D50.1 (K), D60.1 (K), D70.1 (K), EXT_R0.1, U1.21 (PD3), U4.9 (GPIO6)
row1: D11.1 (K), D21.1 (K), D31.1 (K), D41.1 (K), D51.1 (K), D61.1 (K), D71.1 (K), EXT_R1.1, U1.20 (PD2), U4.32 (GPIO27_ADC1)
row2: D12.1 (K), D22.1 (K), D32.1 (K), D42.1 (K), D52.1 (K), D62.1 (K), D72.1 (K), EXT_R2.1, U1.27 (PD7), U4.29 (GPIO22)
row3: D2.1 (K), D13.1 (K), D23.1 (K), D33.1 (K), D43.1 (K), D53.1 (K), D63.1 (K), D73.1 (K), EXT_R3.1, U1.12 (PB7), U4.25 (GPIO19)
row4: D14.1 (K), D54.1 (K), D64.1 (K), D74.1 (K), EXT_R4.1, U1.40 (PF1), U4.22 (GPIO17)
row5: D4.1 (K), D15.1 (K), D25.1 (K), D35.1 (K), D45.1 (K), D55.1 (K), D65.1 (K), D75.1 (K), EXT_R5.1, U1.22 (PD5), U4.10 (GPIO7)
row6: D5.1 (K), D16.1 (K), D26.1 (K), D36.1 (K), D46.1 (K), D56.1 (K), D66.1 (K), D76.1 (K), EXT_R6.1, U1.25 (PD4), U4.31 (GPIO26_ADC0)
row7: D6.1 (K), D17.1 (K), D27.1 (K), D37.1 (K), D47.1 (K), D57.1 (K), D67.1 (K), D77.1 (K), EXT_R7.1, U1.26 (PD6), U4.27 (GPIO21)
row8: D7.1 (K), D18.1 (K), D28.1 (K), D38.1 (K), D48.1 (K), D58.1 (K), D68.1 (K), D78.1 (K), EXT_R8.1, U1.28 (PB4), U4.24 (GPIO18)
row9: D19.1 (K), D29.1 (K), D39.1 (K), D49.1 (K), D59.1 (K), EXT_R9.1, U1.41 (PF0), U4.21 (GPIO16)

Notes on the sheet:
KEY MATRIX
ICSP
RESERVED & TEST PINS
SCREWS to Bottom
SPEAKER
Power Source for devices
LED
Audio C4,5,6 B5,6,7
LOGO
USB
MCU
EEPROM

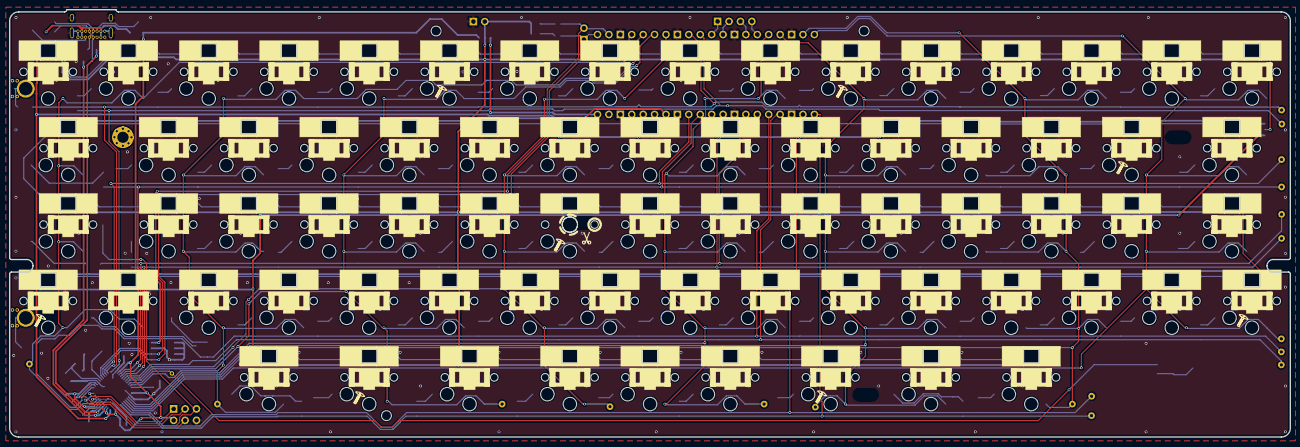
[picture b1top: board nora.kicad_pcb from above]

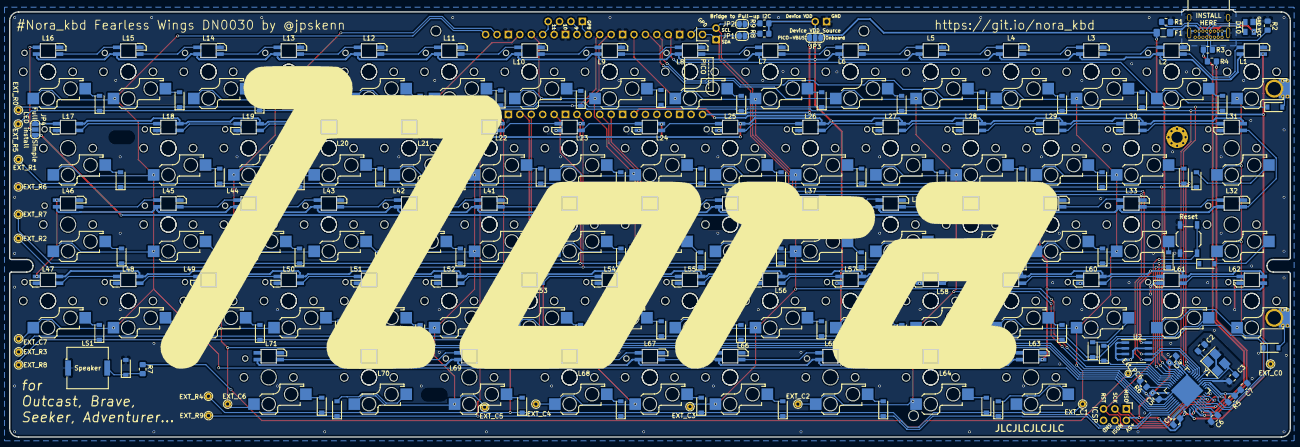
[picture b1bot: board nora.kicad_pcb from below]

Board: 2 copper layers, 285.0 x 95.1 mm, 269 parts (195 on the bottom side), 190 nets.

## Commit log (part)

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2021-12-16 PICO with EEPROM #47
2021-12-16 PICO時、EEPROMの電源をPICO-VBUSからとる#47#16
2021-12-16 PICO #16
2021-12-16 WIP Jonesからボトムプレートを持ってきて、PICO穴をあけてる
2021-12-17 切り取り可能なプレートが必要だが、一旦ここまでとする。
2021-12-17 WIP マトリクス再編成、スイッチ配置
2021-12-18 WIP 配線途中
2021-12-18 WIP VIA打ち始め
2021-12-18 WIP 配線引き終わり
2021-12-18 WIP ダイオードに3Dモデル追加
2021-12-18 WIP PCOひとまず完了
2021-12-18 WIP 不要表示物削除
2021-12-18 WIP 表示レイヤーを変更
2021-12-18 WIP Wide用プレートデータ作成
2021-12-18 プレート作成
2021-12-18 WIP ボトムプレートに切り取りをつけようとしている
2021-12-18 WIP ボトムプレートに切り取りをつけ、さらに改造中
2021-12-18 WIP リセットボタン穴など追加
2021-12-19 ボトムプレート完成
2021-12-19 最終的な配線調整
2021-12-19 発注データ作成
2021-12-19 シルク位置ずれ修正
2021-12-19 Add v03 definition.
    Checked by VIA app.
2021-12-20 WIP バリエーション作成中
2021-12-20 1800と両立させるため、別フォルダを用意
2021-12-20 1800のファイルを元に戻す
2021-12-20 1800とFWの統合Readmeを準備
2021-12-21 補強のため、右のネジ穴付近にシート貼り付け箇所を追加
2021-12-21 RGB Matrix用のLED位置計算
2021-12-21 WIP ビルドガイド更新中
2021-12-21 Implement C6 Audio hardware #54
2021-12-22 スピーカーを追加 #54
2021-12-26 文言変更
2021-12-26 ひとまず全て書き終えた
2021-12-26 Add SW direction silk to PCB front side. #57
2021-12-26 基板おもて側にスイッチの軸形状を模したシルクを追加#57
2021-12-26 フォーマット調整
2021-12-27 参考に追記
2021-12-29 WIP なんとなく、いい具合になってきた
2021-12-29 1800を追加。とりあえず完成
2021-12-30 レイヤー名など整備
2021-12-30 手直ししたロゴを基板に適用
2021-12-30 Refine LOGO #53
2021-12-30 フットプリント変換用アートボード追加
2021-12-30 画像リンク修正
2021-12-30 細かなところを最新に更新
2021-12-30 MCUのシンボルを変更
2021-12-30 WIP DRCエラーなどに対処中
    LEDとSWのフットプリントで、シルク欠けに対応するものへ変更中。
    LEDは上下反転するため、SWのクリックバー穴の処理をどうするか？
2021-12-30 WIP DRCエラーなどに対処中
    LEDとSWのフットプリントで、シルク欠けに対応するものへ変更中。
2021-12-30 WIP DRCエラーなどに対処中
2021-12-31 DRCエラー対応完了
2021-12-31 ビルド例を追加
2021-12-31 WIP 最低限必要な情報に更新中
2021-12-31 写真追加
2021-12-31 メモ削除、ネジ説明追加
2022-01-01 ファームウェアへのリンク変更
2022-01-01 サイズ記載ミス修正
2022-01-01 メモ追加
2022-01-01 solder jumper before shipment, BuildGuide #64
    出荷前に必要箇所をジャンパしておく手順とした。
    サービスマニュアルを追加して、記載した。
2022-01-01 定義ファイル読み込みについて追記
2022-01-02 Expand LED hole #63
    製造の状況によってLED穴がきついことがあるため、余裕を持った穴サイズへ拡大。
2022-01-02 EXT_PC6とEXT_C6の違いが分かりにくいため、Audioピンの名前に変更
2022-01-02 Remove big logo? #60
    小さなロゴに変更
2022-01-02 メッセージ位置微調整 #60
2022-01-02 Update version number.
2022-01-02 Add PRTR silk #62
2022-01-02 アイコンを拡大した #65
2022-01-02 フットプリントを整理
2022-01-02 Enlarge SW sub-hole? #68
    1.7mmから1.8mmへ、5ピンの穴サイズを拡大
2022-01-02 コンスルー高さのチェックが終わったので、2mm以上で決定 #66
2022-01-02 ネーミングとその説明を変更
2022-01-03 Useless center keys on FW. #69
2022-01-03 WIP キー配置を調整中
2022-01-03 WIP キー配置を調整中。LEDとキー減らしたところ
    最下行を外に0.25uずらしたが、右下ネジ穴がソケットパッドに干渉するため、ずらすのをやめる。
2022-01-03 WIP キー配置を調整中。最下行をネジ穴にかぶらないDN0030相当に戻す
2022-01-03 ロゴ位置調整
2022-01-03 右SPCを上下反転してテスト中
2022-01-03 右手側を外へ移動。R-SPC上下反転
2022-01-03 左手側も外へ移動。
2022-01-03 左SPCも上下反転し、左右のSPCは反転とする
2022-01-03 move LED reflection silk from LED to SW footprint #74
2022-01-03 Retry widening R5 #73
2022-01-03 Add Rotary Encoder? #71
2022-01-04 WIP REを配置
2022-01-04 不要メモ削除
2022-01-05 3Dモデル追加とか
2022-01-05 テストピンをスペーサーから離す
2022-01-06 WIP とりあえず全キー埋め。なんとかなるような気がする
2022-01-06 WIP 中央キーのLEDスキップジャンパを追加
2022-01-06 WIP 配線中
2022-01-07 LEDのパッドが短くなっていたのを修正
2022-01-07 NPTHへ変更 #78
2022-01-07 一通り配線完了
2022-01-08 RE配置した基板できあがり #81 #71
2022-01-08 細部調整
2022-01-08 REの枠を追加
2022-01-08 ソケットのシルクに塗りを追加
2022-01-08 #76 Tight? SW plate
2022-01-08 スイッチ穴の横幅を13.8mmから14.2mmに拡大
2022-01-09 シルク、マスク作成
2022-01-09 SplitのSWプレートを作成
2022-01-09 Split w/REのSWプレートを作成
2022-01-09 パターン生成用ファイルをDN0031対応
2022-01-09 JLCPCBでガーバー表示がおかしいため、ネジ穴を独立させた
2022-01-09 Center design for SW Plate #80
2022-01-09 SW plate variation? #79
2022-01-09 Change SW-plate for FW DN0031 #72
2022-01-09 新しいロゴに変更 #61
2022-01-09 "1.8k"ロゴを追加
2022-01-09 FWの基板にバリエーション名を追加 #50
2022-01-09 ネジ穴など、配線禁止エリアをチェック #82
2022-01-09 基板製造ファイル準備
2022-01-09 パーツ番号変更
2022-01-10 ロータリーエンコーダが接続されるマトリクス行を変更
    物理的にREが配置される場所に合わせた行へ修正。
2022-01-10 DN0031用Remap / VIA定義ファイルを追加
2022-01-10 DN0031用、RGB Matrix座標計算を追加
2022-01-10 DN0031用、RGB Matrix LEDインデックスを追加
2022-01-10 Initial DN0031
    Just copied from DN0030
2022-01-10 キット内容まで更新
2022-01-10 TOC更新
2022-01-11 スペーサーシート貼り付けまで
2022-01-11 FW-PCB: Add jumper to skip LEDs with FW+RE layout #85
2022-01-11 不要配線削除
2022-01-11 どのレイアウトの場合にジャンパするかをわかりやすくした #85
2022-01-11 ゴム足マーキングを変更 #83
    - 上（奥）の中央、PICOの切り取りより手前に追加
    - 上、PICOの切り取りの左右を、実線から点線に変更
2022-01-11 取り付けないLEDに枠を追加 #88
2022-01-12 FW+REで取り付けないソケットをわかりやすく #87
2022-01-12 PICOとREを接続 #89
2022-01-12 ケース固定まで修正
2022-01-12 スイッチ足を加工する箇所を追記
2022-01-12 REノブのサイズ指標円の中心が、REの中心とずれていたのを修正
2022-01-12 FW+REのLEDについて追記
2022-01-12 FWのキー数が減ったため、65%の表記をやめた
2022-01-16 親子接続用の6ピンジグザグピンヘッダの例
2022-01-16 R1-R2用の子基板を検討
2022-01-16 親子接続用のフットプリント検討中
2022-01-20 テスト中
2022-01-23 ESDの方向を示すシルクを拡大 #92
2022-01-23 ESDの方向を示すシルクを拡大。中央を狭く
2022-01-23 シルク調整
2022-01-23 LEDの傾きを10度変更して移動し、ネジ穴から少し離した #93
2022-01-23 右下ネジ穴のF.Cuベタを除去 #101
2022-01-28 ステッカー用ロゴ追加
2022-01-28 REのノブサイズの目安を追加
2022-01-28 LEDの穴サイズを縦3.2→3.0mmに変更
2022-01-28 DN0031-Bottom: Move upper small leg position #110
2022-01-28 ネジ頭にかぶらない位置へ、小さいゴム足の貼り付け位置を移動 #110
2022-01-28 DN0031-PCB: Add ”RE” related silk to R5 center socket #109
2022-01-28 REとFWで異なるソケットの配置をわかりやすくした #109
    最下段中央REのソケット
    斜線パターン
    RE→○
    R3中央REのソケット
    クロスパターン
    RE→×
2022-01-28 ステッカー用ロゴの保存忘れ
2022-01-28 DN0031-PCB: Add icon to "upside down" switch #119
2022-01-28 上下反転アイコンを追加 #119
2022-01-28 DN0031-PCB: NPTH to PTH at rotary encoder leg #107
2022-01-28 RE足の穴をNPTHからPTHに変更し、配線調整した #117
2022-01-28 DN0031-PCB, Bottom: For lower height, remove F.Cu and B.Cu at connection spacer area. #105
2022-01-28 すべてのネジ穴に配線、銅箔禁止エリアを配置した #105
2022-01-28 ”RE→×”の文字を入れるだけにとどめる #97
2022-01-28 配線調整
2022-01-28 LED用ジャンパ位置を伝えるシルクを追加 #115
2022-01-28 LED用ジャンパ位置を伝えるシルクを追加 #115 保存忘れ
2022-01-29 DN0031-SW-Plate: Limited spacer sheet length #103
2022-01-29 スペーサー貼り付け幅を狭くして、応力分散するような位置へ移動した #103
2022-01-29 DN0031-SW-Plate: Close R3 right side frame #100
2022-01-29 R3右側の枠を、左側同様に閉じた。REの穴、縦を少し縮めた。 #100
2022-01-29 スペーサー配置箇所の銅箔除去。バージョン更新 #105 #120
2022-01-29 バージョン更新 #120
2022-01-29 C1のパーツ番号を変更 #96
    同じ部品だと思うのだが、以前の番号のものはExtend Partsになっている。
2022-01-29 DN0031-PCB: More space for wiring #98
2022-01-29 配線を穴から離したり調整
2022-01-29 電源を二重化した #121
2022-01-29 DN0032の前に、DN0031を作る
2022-01-30 WIP: LED取り付けまで
2022-01-30 WIP：スペーサーシート貼り付け
2022-01-30 WIP: RE関連
2022-01-30 WIP：RE取り付け
2022-01-30 WIP：スイッチプレート取り付け
2022-01-30 WIP:ケースへの取り付け
2022-01-30 WIP: 仕上げ
2022-01-30 WIP: フォーマットとか
2022-01-30 WIP: REレイアウトのファームウェア書き換え
2022-01-30 リンク変更
2022-01-30 ひとまず書き上がり
2022-01-31 軽微な表現修正
2022-01-31 REノブ取り付け
2022-01-31 エンコーダの回転をRemap/VIAで仮想機キーに割り当てるメモを追加
2022-02-02 レイアウト別の写真を追加
2022-02-02 キーボード定義ファイルについて追記
2022-02-02 細かいところを変更中
2022-02-02 Kailhキーキャップの干渉関連の表現変更
2022-02-03 RGB Matrixでの動作のため"none"に変更
2022-02-03 試作版の注意事項を追加
    正式版ではなくなる項目
2022-02-03 個数の表現を変更
2022-02-03 レイアウトを決める手順を追加
2022-02-04 Remapへ登録したので、定義ファイルの読み込みの説明を削除
2022-02-04 Remapでファームウェアを書き換える方法をメインにする
2022-02-04 目次更新
2022-02-04 ファームウェアのページへリンクした
2022-02-04 Remapでの書き換え手順の説明をわかりやすく
2022-02-04 参考資料に固まる話を追記
2022-02-05 部品の写真を更新
2022-02-05 TODOコメント削除
2022-02-05 リンク間違い修正
2022-02-05 初期ファームウェアの機能
2022-02-05 DN0031-PCB: Pad and via not too match close. #125
2022-02-05 配線、via調整
2022-02-05 #125
2022-02-06 キーキャップのサイズ、確認済みキーキャップを追記
2022-02-07 ファームウェアのリンク先を変更
2022-02-07 DN0031関連の更新
2022-02-07 見切れるため、通常の段落に変更
2022-02-08 ビルド例を追加、整理
2022-02-10 アイコンでなんとか表現しようとしている
2022-02-10 LEDには"NO"アイコンをつけ、すべてをアイコンで表現した
2022-02-10 配線、シルク調整
2022-02-10 視認性向上のため、アイコンサイズを拡大
2022-02-10 追加購入したりできるよう、同梱部品の品番などを追記 #130
2022-02-11 ボトムのリセット穴を拡大して、Noraのリセットスイッチを押せるようにした #132
2022-02-11 fix TYPO
2022-02-11 トップ画像をFearless Wingsに変更
2022-02-11 Fullレイアウト用データ作成
2022-02-11 Fullレイアウト用プレート作成
2022-02-11 改行忘れ
2022-02-11 プレート名称変更 #134
2022-02-11 DN0032のビルドガイドをDN0031で置き換え。再スタート
2022-02-11 バージョン表記変更
2022-02-11 シートを500+160mmに増量 #131
2022-02-12 キーキャップのガイドを作成中
2022-02-12 REレイアウトのファームウェア書き換えを削除
2022-02-12 最下行中央のキーをREから外す
2022-02-12 CADデータ変更
2022-02-12 #137
2022-02-12 #136
2022-02-12 WIP アイコン配置、シルク調整
2022-02-12 Fullレイアウトを含むため、ボード名からFWを除去
2022-02-12 プレート類のガーバーファイル準備
2022-02-12 DN0031-PCB: Add PTH to RE side switches #138
2022-02-13 REの端子穴を拡大して、スイッチの足が入るようにした #138
2022-02-13 PCBのガーバーファイル準備 #118
2022-02-13 パーツ番号を在庫に合わせて変更
2022-02-13 JLCPCB以外の業者向け、プレート類のガーバーファイル準備
2022-02-13 FWロゴ復活 #140
2022-02-13 スペーサーシートの長さ検証
2022-02-13 WIP DN0032
2022-02-13 キャプション間違いを修正
2022-02-13 DN0032用VIA定義ファイルを用意
2022-02-13 レイアウトのマーキングを再考し、変更
    Fullはすべて取り付けるのでマーク不要。
    FWとREでLEDの取り付けが違う場所を強調。
2022-02-13 LED取り付けまで
2022-02-13 サービスマニュアル
2022-02-14 細かな表現変更
2022-02-16 Fullレイアウトなどについて
2022-02-16 レイアウト画像変更
2022-03-14 remove old photos
2022-03-14 リモート作業を反映
2022-03-14 WIP とりあえず写真を載せる
2022-03-15 体裁修正、メモ追加
2022-03-20 スイッチプレート穴サイズ、横14.2→14ｍｍに変更
2022-04-11 PICO取り付け部品を追記
2022-04-12 わかりやすく
2022-04-12 型番追記
2022-04-12 ゴム足（大）をキットに含む
2022-04-13 memo
2022-04-13 写真更新
2022-04-13 トップ写真変更、ビルド例追加
2022-04-13 不要ファイル削除
2022-04-13 写真追加、メモ追加
2022-04-14 Adjust GPIO pin assign
2022-04-14 マトリクス初期化の書き方を変更
    キーマップを普段使っているものに変更
2022-04-14 キーマップ修正
2022-04-14 LEDの注意書き追加
2022-04-14 PICO取り付け
2022-04-15 PICO追記
2022-04-18 初期ファームウェアについて更新
2022-04-19 一般的に販売されているキーボードとの比較写真に変更
2022-04-19 手順を修正
    ファームウェアの書き換えを、
    ”キーボード”として組み上げてから行うことも想定。
2022-04-20 表現変更
2022-04-22 スペーサー必要数の間違いを修正
2022-04-22 左右対称のレイアウトの比較写真を追加
2022-04-23 説明をわかりやすく
2022-04-23 概要更新
2022-04-23 バージョン表記
2022-04-26 gitignore
2022-04-26 キーキャップについての記述を更新
2022-05-03 ボトムプレートと基板の制振
2022-05-03 ファームウェア更新を追記中
2022-05-07 v1用にファイル名変更
2022-05-07 関連ファイルを更新
2022-05-07 Remapでファームウェアを書き込む方法を更新。
2022-05-07 レイアウト変更を更新
2022-05-07 不要コメント削除
2022-05-07 LEDのトラブルシュートを更新
    USB電源は出荷前にジャンパしていることと、
    ここが接続されていなければMCUも動作しないため、
    原因には当てはまらない。
2022-05-08 ふりがな追加
2022-05-09 ノブサイズの記載間違いのため、画像差し替え
2022-05-09 わかりやすい表現に
2022-05-09 左右対称のみをアピールするため不要
2022-05-09 目次追加
2022-05-09 リンクミス、キャプション修正
2022-05-09 履歴更新
2022-05-09 最新版と過去版のビルドガイドをわかりやすく
2022-05-09 体裁変更
2022-05-09 開発停止をわかりやすく
2022-05-09 asideタグやめ
2022-05-09 コンセプト追加
2022-05-09 TYPO
2022-05-09 リンク追加
2022-05-09 SemiErgoに言及
2022-05-09 どういうおすすめなのかを具体的に
2022-05-09 可読性向上
2022-05-09 目次調整
2022-05-09 リスト順を変更
2022-05-09 全キーを主張
2022-05-09 単体でアクセスできるよう、キーキャップ選び方ガイドを別ドキュメントとした
2022-05-09 リンク修正
2022-05-09 ファイル名Typo修正
2022-05-10 姉妹機を明記
2022-05-10 基板＝PCB
2022-05-11 キャプション修正
2022-05-11 取り付け例の写真を追加
2022-05-12 LED方向のシルクを拡大 #155
2022-05-12 どのレイアウトを対象に作業しているかを明示
2022-05-12 絵文字テスト
2022-05-12 重複した説明を修正
2022-05-12 絵文字追加
2022-05-12 ボトムプレートの状態を説明
2022-05-12 ”くわしい説明”を目立つように
    GitHub上で表示した際に、
    ▶︎
    の展開マークが表示されず、目立たないのをなんとかした。
2022-05-12 スイッチのはめ込み具合について表現を変更
2022-05-12 組み立て時のキー配置の参考リンクを追加
2022-05-13 #157
2022-05-13 とりあえず通常スイッチに適用
2022-05-13 #158
2022-05-13 #147
2022-05-14 小さな文字を拡大
2022-05-14 KLEへのリンクを追加
2022-05-15 スイッチ上下反転を強調
    上下を間違えてスイッチを取り付けようとして、はんだ付け済みLEDをランドごとはがす事故が発生したため、強調。
2022-05-16 #162
2022-05-16 左右スペースのLEDをスキップするジャンパを追加
2022-05-16 シルク調整、#155のパーツ指定忘れ対応
2022-05-21 v.1販売開始時のQMKソースへのリンク追加
2022-05-25 トップ写真を見栄え良く
    遊舎工房の商品写真に合わせた
